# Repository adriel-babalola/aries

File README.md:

# Aries: Compact CO2 Air Quality Sensor

**Aries** is a compact, battery-powered air quality monitoring device that measures CO₂ levels via a beautiful circular 1.28" TFT display. Built around the **Seeed Studio XIAO ESP32-C3**, it features the Sensirion **SCD40** CO₂ sensor and displays real-time air quality data with WiFi/Bluetooth connectivity.

Went for the name aries beacause i thought it was the Egyptian god of the Air, tunred out the actual name i was looking for was Horus, but i was already in too deep, so i went with Aries.

## Features

- **Real-time CO₂ Monitoring**: Sensirion SCD40 sensor with high accuracy (±50 ppm over 400–2000 ppm)
- **Display**: 1.28" circular GC9A01 TFT display (240×240)
- **Portable**: Runs on a 3.7V LiPo battery (1000 mAh)
- **Smart Power Management**: Slide switch for manual on/off without desoldering
- **Wireless**: WiFi + Bluetooth (BLE 5.0) via ESP32-C3 for data logging or mobile app integration
- **PCB**: 2-layer design optimized for component placement
- **3D-Printed Enclosure**: Base and Lid

## Hardware Overview

### Core Components

| Component | Model | Purpose |
|-----------|-------|---------|
| **Microcontroller** | Seeed XIAO ESP32-C3 | Brain of the device; manages display & sensor |
| **CO₂ Sensor** | Sensirion SCD40-D-R2 | Measures atmospheric CO₂ (I2C interface) |
| **Display** | GC9A01 1.28" TFT | Circular 240×240 RGB display (SPI) |
| **Battery** | 3.7V 1000 mAh LiPo | Portable power (503450 or 603040 form factor) |
| **Power Switch** | Slide/Toggle | On/off control on battery line |

### PCB Design

**Schematic**

**PCB**

### Case Design

The enclosure consists of three 3D-printed parts:

1. **Case** (`aries_casing_full.f3z`): Main body that houses the PCB and display

2. **Base** (`base.f3z`): Bottom mounting plate

3. **Lid** (`lid.f3z`): Top cover with display cutout

## Bill of Materials

| Component | Value | Qty | Supplier | Original Price | Final Price |
|-----------|-------|-----|----------|-----------------|-------------|
| PCB + PCBA (SCD 40) | 5 PCB + 2 PCBA | 7 | [PCBWay](https://www.pcbway.com/) | $72.48 | $72.48 |
| Xiao ESP32-C3 | — | 1 | [Seeed Studio Store](https://www.aliexpress.com/item/1005007039705247.html?spm=a2g0o.cart.0.0.3c3838da85i9NG&mp=1) | $10.77 | $4.63 |
| LiPo Battery | 3.7V 1000mAh | 1 | [Rainpro Store](https://www.aliexpress.com/item/1005005244012524.html?spm=a2g0o.cart.0.0.3c3838da85i9NG&mp=1) | $4.40 | $3.34 |
| Power Switch | SS12D06G5 3-Pin | 1 | [DQLZV Store](https://www.aliexpress.com/item/1005006258365679.html?spm=a2g0o.cart.0.0.3c3838da85i9NG&mp=1) | $1.42 | $1.39 |
| Circular TFT Display | 1.28" GC9A01 | 1 | [Shenzhen Chip Store](http://aliexpress.com/item/1005005925857858.html?spm=a2g0o.cart.0.0.3c3838da85i9NG&mp=1&pdp_ext_f=%7B%22cart2PdpParams%22%3A%7B%22pdpBusinessMode%22%3A%22retail%22%7D%7D) | $3.92 | $2.42 |
| M2.5 Screws | 10mm x50pc | 1 | [ScrewMax Supply Store](https://www.aliexpress.com/item/1005012931823427.html?spm=a2g0o.cart.0.0.3c3838da85i9NG&mp=1) | $1.63 | $1.60 |
| Soldering Wire | 50g 0.6mm | 1 | [JCD Official Store](https://www.aliexpress.com/item/1005006030104628.html?spm=a2g0o.cart.0.0.3c3838da85i9NG&mp=1) | $2.37 | $2.30 |
| AliExpress Shipping | — | — | [AliExpress](https://www.aliexpress.com/) | — | $8.69 |
| **TOTAL COST** | | | | | **$106.50** |

### Display Guide

A full guide to working with the GC9A01 circular display and ESP32-C3 is available here:  
🔗 [Bench: XIAO ESP32-C3 + 1.28" Circular TFT](https://thesolaruniverse.wordpress.com/2024/04/02/bench-featuring-a-seeed-studio-xiao-esp32-c3-and-a-1-28-spi-gc9a01-circular-tft-display/)

## Inspiration & References

This project draws from several open-source projects and guides:

- **Seeed Studio** - XIAO ESP32-C3 ecosystem and examples
- **Sensirion** - SCD40 sensor datasheet and Arduino library
- **@notaroomba** - GitHub README structure and best practices
- **@GarageTinkering** - 3D CAD enclosure design tutorial ([YouTube](https://www.youtube.com/@GarageTinkering))
- **The Solar Universe Blog** - GC9A01 display integration guide

and may the Odds ever be in your favor

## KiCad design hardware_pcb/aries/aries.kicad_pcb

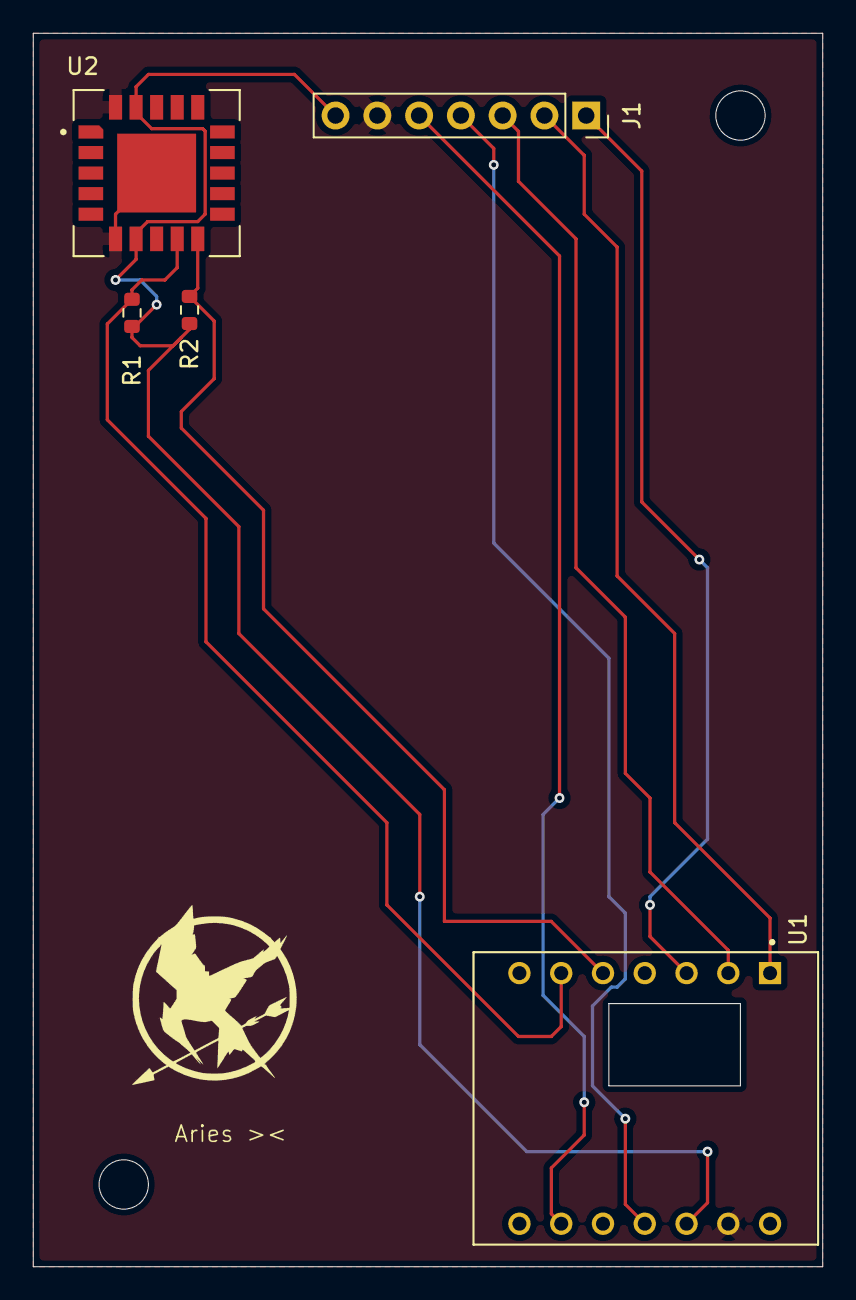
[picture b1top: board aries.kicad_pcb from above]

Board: 2 copper layers, 48.0 x 75.0 mm, 5 parts (0 on the bottom side), 9 nets.

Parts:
J1: Conn_01x07_Socket (TFT Display); PinSocket_1x07_P2.54mm_Vertical
R1, R2: 10k; R_0603_1608Metric
U1: XIAO_ESP32C3; MODULE_XIAO_ESP32C3
U2: SCD40-D-R2; XDCR_SCD40-D-R2

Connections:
/CS: J1.2, U1.1 (D0)
/DC: J1.3, U1.2 (D1)
/MOSI: J1.4, U1.11 (D10)
/RST: J1.1, U1.3 (D2)
/SCL: R1.2, U1.6 (D5), U2.9 (SCL)
/SCLK: J1.5, U1.9 (D8)
/SDA: R2.2, U1.5 (D4), U2.10 (SDA)
/VCC_3V3: J1.7, R1.1, R2.1, U1.12 (VCC_3V3), U2.7 (VDD), U2.19 (VDDH)
GND: J1.6, U1.13 (GND), U2.6 (GND), U2.20 (GND), U2.21 (GND)

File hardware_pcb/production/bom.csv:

Designator,Footprint,Quantity,Value,LCSC Part #
"R1, R2",0603,2,10k,
U2,XDCR_SCD40-D-R2,1,SCD40-D-R2,
